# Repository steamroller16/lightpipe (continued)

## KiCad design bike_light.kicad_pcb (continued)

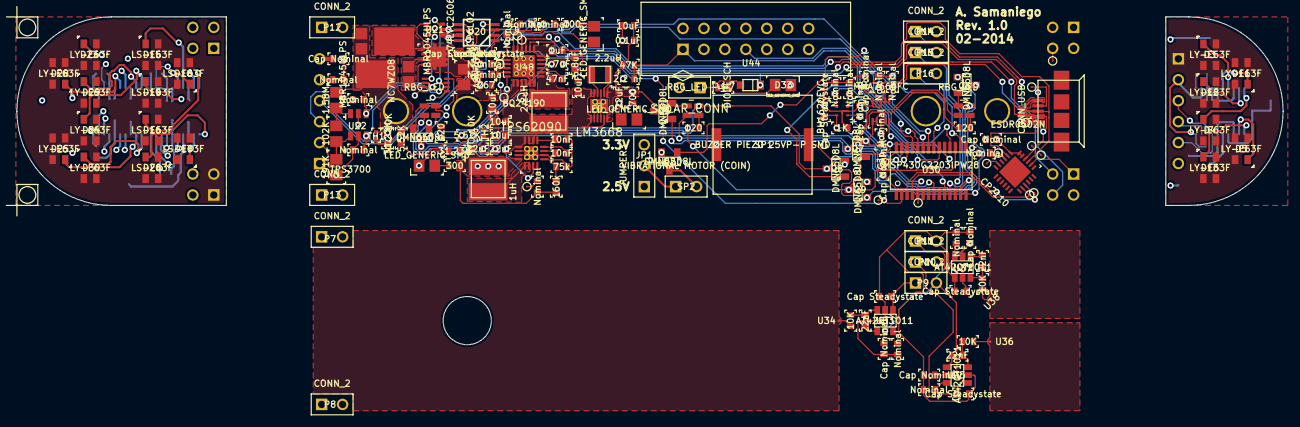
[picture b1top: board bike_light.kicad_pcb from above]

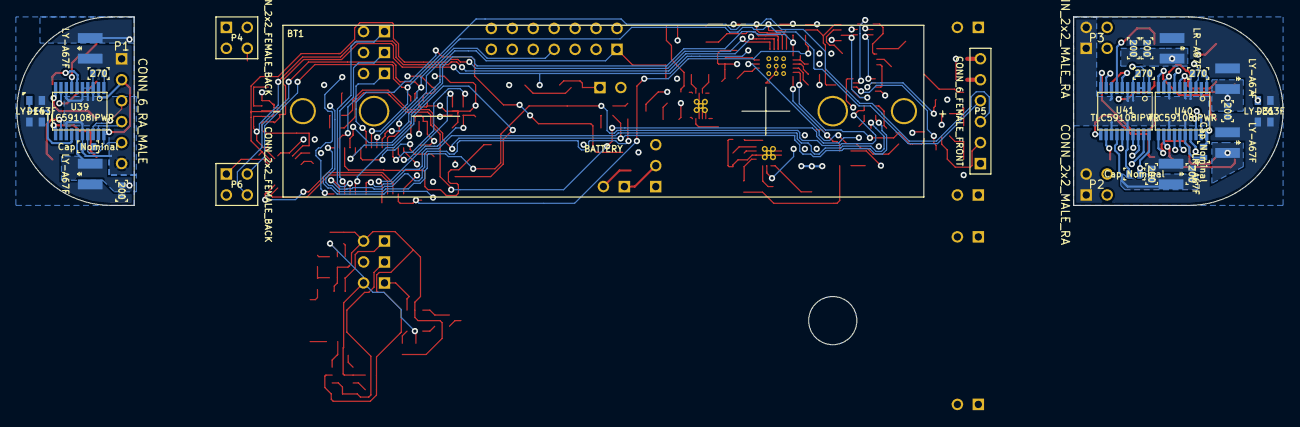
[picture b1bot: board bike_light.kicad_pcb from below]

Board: 4 copper layers, 153.5 x 39.8 mm, 198 parts (30 on the bottom side), 121 nets.

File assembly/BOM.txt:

Ref.	Part	Qty.
BT1	BATTERY	1
"C1,C2"	Cap Steadystate	2
"C3,C4"	Cap Nominal	2
C5	Cap Steadystate	1
"C6,C7"	Cap Nominal	2
C8	22nF	1
C9	Cap Steadystate	1
C10	Cap Nominal	1
C11	22nF	1
C12	Cap Steadystate	1
C13	Cap Nominal	1
C14	22nF	1
C15	Cap Steadystate	1
C16..C20	Cap Nominal	5
"C21,C22"	22uF	2
"C23,C24"	10nF	2
C25	10uF	1
C26	22uF	1
C27	0.1uF	1
C28	10uF	1
C29	2.2 nF	1
C30	Cap Nominal	1
C31	1uF	1
C32	6.8uF	1
C33	47nF	1
C34..C36	10uF	3
C37	4.7uF	1
"D1,D2"	MBR1045ULPS	2
D3..D5	LY-E63F	3
D6	LY-A67F	1
D7..D9	RBG_LED	3
D10	LY-A67F	1
D11..D14	LY-E63F	4
D15..D20	LS-E63F	6
"D21,D22"	LR-A67F	2
D23..D25	LY-E63F	3
"D26,D27"	LY-A67F	2
D28..D31	LY-E63F	4
D32	LED_GENERIC_SMD	1
D33	DIODESCH	1
D36..D38	LED_GENERIC_SMD	3
JP1	JUMPER3	1
L1	1uH	1
"L2,L3"	2.2uH	2
P1	CONN_6_RA_MALE	1
"P2,P3"	CONN_2x2_MALE_RA	2
P4	CONN_2x2_FEMALE_BACK	1
P5	CONN_6_FEMALE_FRONT	1
P6	CONN_2x2_FEMALE_BACK	1
P7..P16	CONN_2	10
P17	SOLAR_CONN	1
Q1	AON7611	1
Q2..Q9	DMN65D8L	7
R1	R	1
R2	1.58M	1
"R3,R4"	Nominal	2
R5	102K	1
R6	191K	1
R7..R12	200	6
R13	1.55K	1
R17	1K	1
R18..R21	Nominal	4
R22	10K	1
R23	Nominal	1
R24	10K	1
R25	Nominal	1
R26	10K	1
R27	Nominal	1
R28..R30	120	3
R37..R39	270	3
R40	Nominal	1
R41	160k	1
R42	300	1
R43	Nominal	1
R44	75k	1
R45	700	1
R46	47K	1
R47	Nominal	1
R48	700	1
R49..R52	Nominal	4
"R53,R54"	5.52K	2
R55	267	1
R56	Nominal	1
"R57,R58"	31.23K	2
SP1	BUZZER PIEZO 25VP-P SMD	1
SP2	VIBRATIONAL MOTOR (COIN)	1
"TH1,TH2"	NTC 10K	2
U1..U19	TEST_PT	19
U20	MCP6L02	1
U21	74LVC2G06	1
U22	TPS3700	1
U23	NC7WZ08	1
U30	MSP430G2203IPW28	1
U31	BH1620FVC	1
U32	MMA7660FC	1
U33	AT42QT1011	1
U34	TOUCHPAD	1
U35	AT42QT1011	1
U36	TOUCHPAD	1
U37	AT42QT1011	1
U38	TOUCHPAD	1
U39..U41	TLC59108IPWR	3
U42	TPS62090	1
U43	LM3668	1
U44	CONN_JTAG_14_2_wire	1
U45	CP2110	1
U46	ESDR0502N	1
U47	CONN_USB	1
U48	BQ24190	1

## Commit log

2013-10-22 First test commit.
2013-10-23 Does this shiet work???
    EXTENDEDDDDDD
2013-10-23 Kicad files
2013-11-07 Started working through components
    Going through the parts list from top to bottom. Got to the light
    sensor. Not done yet.
2013-11-08 Accelerometer done!
    progressin' like a beast
2013-11-10 Safety Lighting done!
    mmm getcha some of dis lighting... for safety...
2013-11-11 Various components added
    USB conn, general outputs, brake signal, touch sensor
2013-11-12 Battery management stuff
    :D
2013-11-15 random minor thing
2013-11-17 Added comments to schematic
    shows what needs to be done
2013-11-18 revised LED parts to match reality
2013-11-23 fixed mosfet battery direction ic
2013-11-24 started fleshing out USB comm circuits
2013-11-24 added missing datasheets to old components
2013-11-24 completed USB comm circuits
2013-11-25 started working on charging IC
    can't for the life of me tell if it will work with low battery
    voltage... seems like it might work, but it won't start switching until
    the battery voltage is above 3.3V, in which case it acts as a buck
    regulator to 3.3V. That 3.3V is adjustable, however, so if we can get
    away with 3.0V on the other IC's which we need to power, we might be
    okay... It will boost the battery voltage up to 5V if a usb device is
2013-11-30 3.3V supply done.
2013-11-30 Removed bak and bck files.
2013-11-30 Added a rules file to ignore bak and bck files.
2013-11-30 Removed another bak file.
2013-11-30 Added .gitattributes file to handle line endings correctly.
2013-11-30 save current sheet only test
2013-11-30 save whole schematic project test
    worked!
2013-11-30 deleted crap files
2013-11-30 added part info for power IC
2013-12-02 added MSP to proc sheet
2013-12-05 added bat-current LED driver array for I2C
2013-12-06 finished batt-current LED driver array over I2C
2013-12-07 added headlight sheet, led, dac
2013-12-07 organized proc sheet I/O, organized I2C bus structure
2013-12-08 continued fleshing out proc
2013-12-08 general organization, fixed power reg sheet, added jtag
2013-12-09 removed crap file
2013-12-10 2.5V Regulator finished.
2013-12-10 added thermal pad to 2.5V, added some labels
2013-12-11 Minor fixes, labels, etc
2013-12-12 started working on charging IC
2013-12-13 continued working on charging IC
2013-12-13 uh. same as before? some glitch
2013-12-14 finished schematic charger, need to part out caps and inductor
2013-12-18 added pullups/downs as necessary, added test pts
    also added interrupt conn to msp from charger, made led part for generic
    indicators, added generic indicators to psu's
2013-12-19 fixed issue with test point symbols
2013-12-20 various fixes due to issues found in ERC
    learned how to use invisible pins
2013-12-21 started figuring out how to get pcb going
    also need to figure out how to make some footprints, although there is a
    nice library of footprints avalible already
2014-01-13 gave parts unique id's
2014-01-18 finished making footprints!
    :D
2014-01-18 placed components ... quite the task!
    there is a lot of shit going on in this board... :D
2014-01-19 trying to pack stuff in...
2014-01-19 Never thought 0805 would seem big...
    But about 80% of the space is consumed by the 0805 resistor and caps.
    01005? XD
2014-01-20 moving around parts in pcb
2014-01-31 pdf revision
2014-02-01 revisions to board and sch
2014-02-01 revised layout considerably. more compact
    almost ready for routing
2014-02-03 replacement of parts, moved parts, preparing for routing
2014-02-04 organizing parts...
2014-02-07 rearranged components, revised footprints
    also planned power/gnd planes. haven't routed anything yet
2014-02-08 parts arranged plausibly
    maybe ready for routing?
2014-02-09 revised connections between boards
    now right and left will be identical and easy to assemble.
2014-02-10 began routing!!!!!
    :D
    gonna try the autorouter after important traces.
2014-02-10 did 1 trace...
2014-02-13 routed 70% of board, made adjustments to schematics as necessary
2014-02-16 routed the back light module
2014-02-16 finished other light module
2014-02-17 finished routing board, added vibrator module
2014-02-22 revised board for manufacture
    still need to panelize
2014-02-24 made minor revisions for manufacture
    just need to panelize, double check parts, and order
2014-02-27 found error in schematic, charger stat LED
2014-03-01 added connector for testing solar panel
2014-03-01 added solar panel indicator and protection diode
    need to annotate, add parts, update netlist, and complete layout
2014-03-01 completed rev 1 of board
    need to panelize
2014-03-02 rearranged manufacturing file structure
    board completed for rev 1. sent out for manufacture. ordered parts.
2014-03-02 birth of the new codebase :D
2014-03-06 added some preview pngs of the board ^-^
2014-03-06 tiny change in code plan
2014-03-07 added note about time sync between devices
2014-03-08 code plan update with pins and addresses
2014-03-09 started working on the code
2014-03-10 started coding. not sure about file structure
    much to be done. see main.c
2014-03-12 file structure commit
2014-03-12 forgot to commit main.c
2014-03-12 initial code commits
2014-03-13 minor shiet, not much time today
2014-03-13 wrote util adc/gpio, other minor corrections
2014-03-14 Added empty header files.
2014-03-15 pins and gpio util done (?)
2014-03-15 jus' codin'.
2014-03-15 renamed some files... trying to outline desired behaviors in main.c
2014-03-15 added functionality outline in top of main.c
2014-03-15 batt_voltage sensor fleshed out
2014-03-16 started working on the timers...
2014-03-16 realized issue with timer pin out
    I don't think there is hardware support to do the RGB color control with
    indpendent duty cycles. We might have to steal one of the other LED ctrl
    outputs in order to do that, or make a hack solution in software...
2014-03-16 Added IAR project file. Code doesn't compile yet.
2014-03-16 Removed some unnecessary IAR files.
2014-03-16 Lots of changes to main, isr, and util_adc. They all compile now. May or may not work.
2014-03-16 Added header files to iar project.
2014-03-17 drafted timers. problems in there though with RGB mixing
2014-03-23 finished drafting the code for feedback lights
2014-03-24 finished(really) the feedback LED setup
2014-03-24 implemented RGB battery fuel guage LED
2014-03-31 various code additions
2014-06-01 Added assembly files
2014-06-01 ignore random files
2014-06-01 Rearranged ref des for assembly outputs
2014-06-08 Added code for initial debug and testing
    All in main.c and main.h. Includes testing for the touch pads, for the
    RGB led's, and for the signal flash timer logic. Does this using the
    watchdog timer. Proc in LPM3, rest through interrupts.
2014-06-08 ignore random file
2014-06-08 Added vibration debug code
2014-06-08 added speaker debug
2014-06-08 Added project file from older version of IAR workbench.
2014-06-08 main.c now compiles.
2014-06-08 Added util_adc and util_i2c. Both compile.
2014-06-08 I2C is much better looking now. Still not tested.
2014-06-13 debug code revisions
2014-06-13 debug code revisions attempt 2
2014-06-14 project file changes in IAR
2014-06-14 Revert "debug code revisions attempt 2"
    This reverts commit d0ee1208265ca8849124d270e9b8d0178f3eb694.
    Conflicts:
    code/src/main.c
2014-06-15 gah, reverting changes, getting ready for first run
2014-06-15 started debugging, fixed project file
2014-06-16 New: Touch, debug LED's, clicker, wdt interval
    minimally functional demo of touch enabled signaling, using wdt timer as
    the means for switching a debug LED on and off. click feedback enabled
    through buzzer. interrupt driven LPM3.
2014-06-16 SAM- HELP? added various I2C debug stuff
    need help using some of your functions
2014-06-17 still not working... ptrs- oh my.
2014-06-17 Quick fixes to i2c debug code to fix datatypes.
2014-06-18 small changes. still compilation issues.
    something related to argument types within the functions in i2c.c I
    didn't get much of a chance to debug today, so I can check tomorrow
2014-06-18 data type conflicts resolved. compiles, but...
    USCIAB0TX interrupt is never firing. Need to do some digging and figure
    out why.
2014-06-20 hack-y but FLASHING FRIGGING BRIGHTLY
    :deciduous_tree: ?
2014-06-21 added i2c all call for light demo
2014-06-21 started fleshing in batt comm
2014-06-21 update util i2c
2014-06-22 I2C - BROKEN...
    gets stuck in an infinite loop where the write function gets called over
    and over. If I single step then everything works as intended. If I let
    the chip run, then the I2C LED's never turn on. The older code worked,
    but I don't like the way it was written. It really needs to be
    non-blocking.
2014-06-23 Demo of WDT for low freq interrupts
    For use with signal flashing. I am trimming down the code into different
    branches which are functional so as to squash bugs. This code has been
    tested and seems to work for low freq interrupts, which will be used for
    signal flashing.
2014-06-24 I2C Write demo w/ I2C LED's
    Works with older code (committed here). Trying to figure out why my new
    code (commented - which I think is cleaner) doesn't work. Problem with
    writing has been isolated to I2C ISR. Also, figured out that the way to
    turn the LED's on and off is with their LEDMODE bits, rather than by
    turning on/off the MODE1 oscillator bit. The latter results in glitches
    during operation.
2014-06-25 I2C Write - works. Set Slave Adr - works.
    working on read command now.
2014-06-25 problems with I2C read...
    needs revising
2014-06-26 I2C Write/Read single/multi works.
    Added some code for demo in main.
2014-06-26 started interfacing with charger IC
    defines moved to chip~.h, filled in battery info and charger info, just
    need to write the commands using i2c functions
2014-06-26 finished comms w/ batt chg ic
    also added files to IAR project
2014-06-26 finished comms w/ led drivers
    added chip~.c,.h files for led drivers, updated project file, added
    minimal demos for chip comms, updated i2c files
2014-06-26 pedantic, unnecessary commit
2014-06-27 started accel comms, .h done, working on .c
    . . .
2014-06-28 still working on figuring out init settings
    planning out algorithm also
2014-06-28 finished comms w/ accel
    still needs testing
2014-06-29 started light sense comms
2014-06-29 finished light sense comms
    also modified adc.c isr
2014-06-29 added accel isr
    I guess the port 2 isr should be in main or in its own file, as it
    shares interrupts from the charger, the accel, and the touch inputs?
2014-06-29 added demos in main for testing
2014-06-29 started fleshing in UART comms
2014-06-30 finalized UART comms
    isrs need to be implemented externally so that I2C and UART can share
    the same ISRs
2014-07-01 debugging accel comm.
    Interrupts not firing, hangs with bus low. Seemed to work initially, but
    have since been unsuccessful in reliably communicating.
2014-07-03 started working on algorithm
    made a new file, barely starting out
2014-07-04 No adc! Problems with accel and light sens
2014-08-22 started working in demo of signals
2014-08-23 functional demo created
